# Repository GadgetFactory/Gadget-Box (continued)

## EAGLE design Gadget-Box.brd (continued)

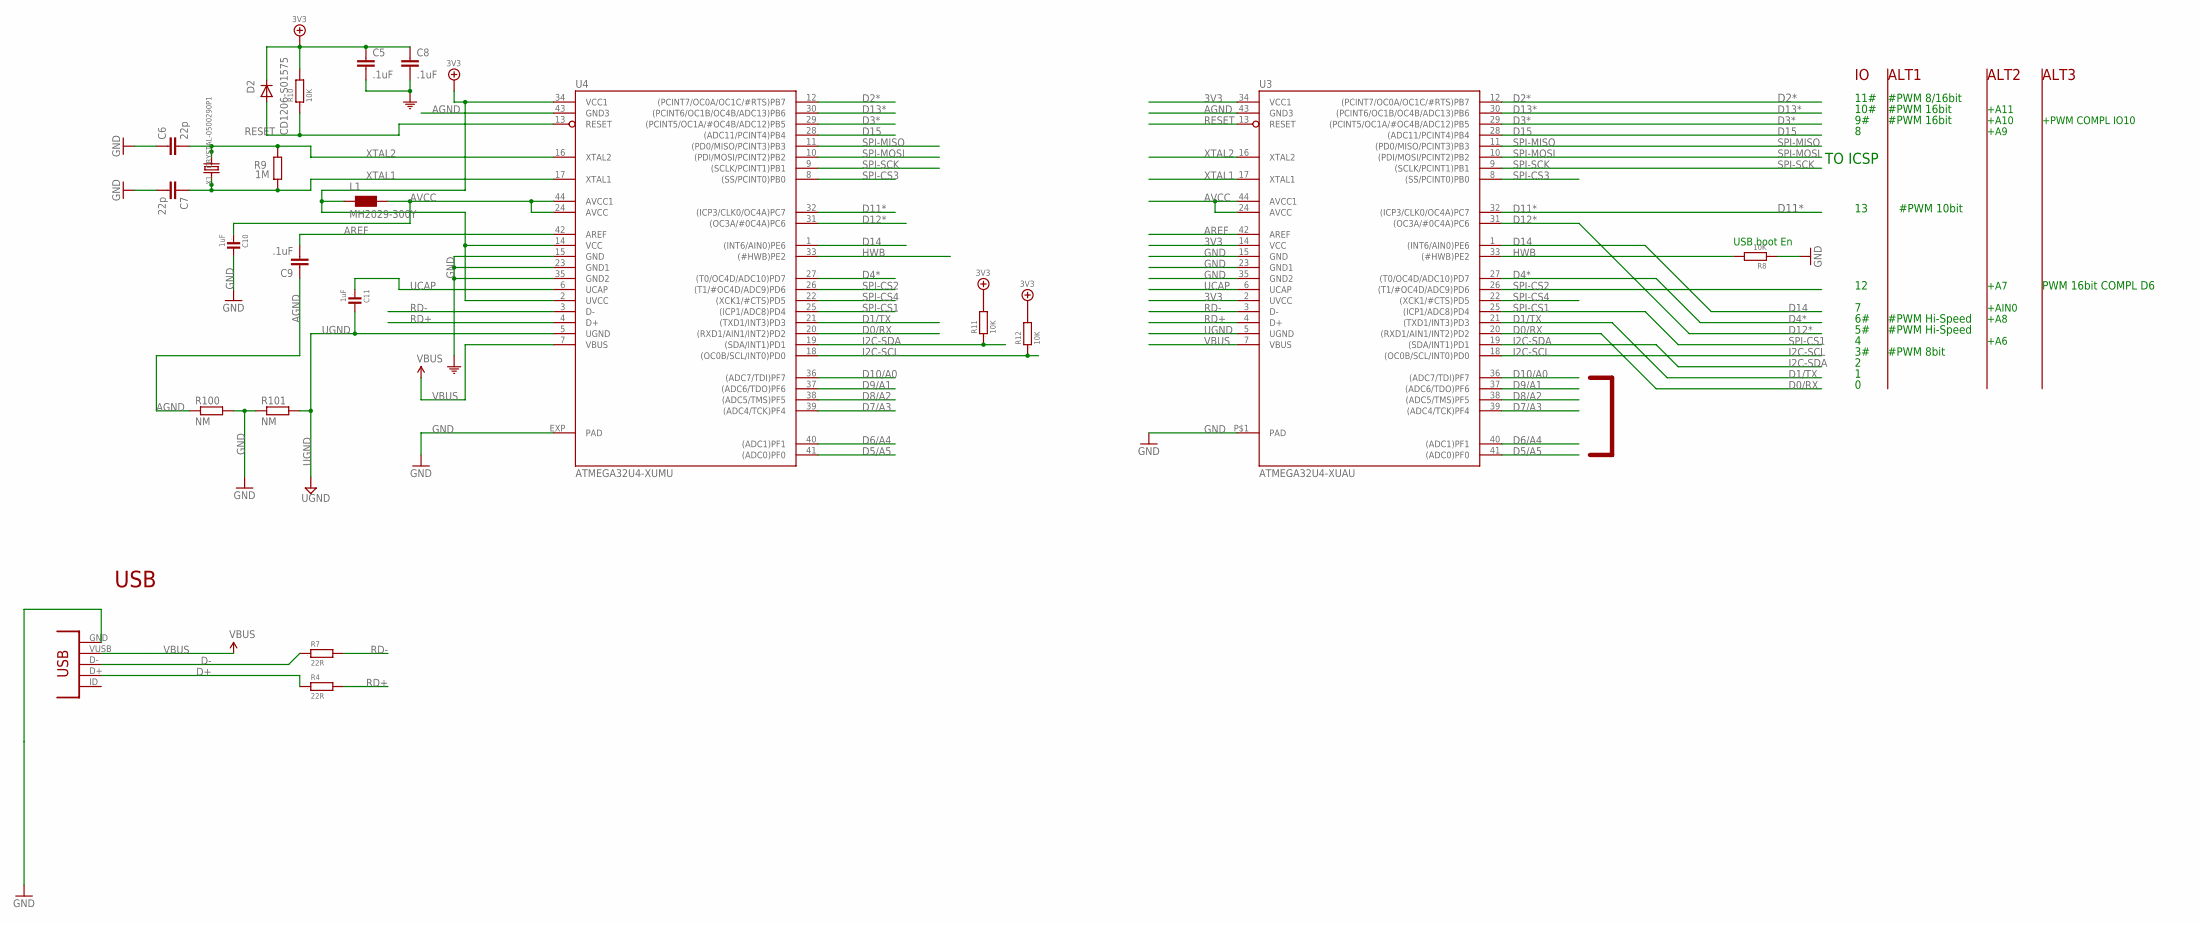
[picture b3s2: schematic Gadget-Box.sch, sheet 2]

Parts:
C5, C8, C9: .1uF; C0603-ROUND; PARTNO GRM188F51E104ZA01D,MURATA ELECTRONICS (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
C6, C7: 22p; C0603-ROUND; PARTNO C1608C0G1H220J080AA,TDK CORPORATION (VA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
C10, C11: 1uF; 0603; PARTNO C1608X5R1A105K080AC,TDK CORPORATION (VA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
D2: CD1206-S01575; MINIMELF; PARTNO CD1206-S01575,BOURNS INC (VA),dk,CD1206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
L1: MH2029-300Y; 0805; PARTNO MH2029-300Y,BOURNS INC (VA),dk,MH2029-3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
R4, R7: 22R; 0805; PARTNO RMCF0805JT22R0,STACKPOLE ELECTRONICS IN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
R8, R10, R11, R12: 10K; 0603; PARTNO RC0603JR-0710KL,YAGEO (VA),dk,311-10KGR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
R9: 1M; R0603-ROUND; PARTNO RMCF0603JT1M00,STACKPOLE ELECTRONICS IN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
R100, R101: NM; R0402
U3: ATMEGA32U4-XUAU; TQFP44-PAD; PARTNO ATMEGA32U4-AUR,ATMEL (VA),dk,ATMEGA32U4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
U4: ATMEGA32U4-XUMU; QFN44ML7X7
USB: CONN_USB; CONN_USB_MINI-B; PARTNO USB-M26FTR,ON SHORE TECHNOLOGY INC (VA)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
X1: CRYSTAL-0500290P1; 2P-SMD-5.0X3.2; PARTNO ABM3-8.000MHZ-D2Y-T,Abracon Corporation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

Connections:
3V3: C5.1, C8.1, D2.C, L1.1, R10.2, R11.2, R12.2, U3.2 (UVCC), U3.14 (VCC), U3.34 (VCC1), U4.2 (UVCC), U4.14 (VCC), U4.34 (VCC1); also elsewhere on the board
AGND: C9.1, R100.1, U3.43 (GND3), U4.43 (GND3)
AREF: C9.2, U3.42 (AREF), U4.42 (AREF)
AVCC: C10.1, L1.2, U3.24 (AVCC), U3.44 (AVCC1), U4.24 (AVCC), U4.44 (AVCC1)
D0/RX: U3.20 ((RXD1/AIN1/INT2)PD2), U4.20 ((RXD1/AIN1/INT2)PD2); also elsewhere on the board
D1/TX: U3.21 ((TXD1/INT3)PD3), U4.21 ((TXD1/INT3)PD3); also elsewhere on the board
D2*: U3.12 ((PCINT7/OC0A/OC1C/#RTS)PB7), U4.12 ((PCINT7/OC0A/OC1C/#RTS)PB7); also elsewhere on the board
D3*: U3.29 ((PCINT5/OC1A/#OC4B/ADC12)PB5), U4.29 ((PCINT5/OC1A/#OC4B/ADC12)PB5); also elsewhere on the board
D4*: U3.27 ((T0/OC4D/ADC10)PD7), U4.27 ((T0/OC4D/ADC10)PD7); also elsewhere on the board
D5/A5: U3.41 ((ADC0)PF0), U4.41 ((ADC0)PF0); also elsewhere on the board
D6/A4: U3.40 ((ADC1)PF1), U4.40 ((ADC1)PF1); also elsewhere on the board
D7/A3: U3.39 ((ADC4/TCK)PF4), U4.39 ((ADC4/TCK)PF4); also elsewhere on the board
D8/A2: U3.38 ((ADC5/TMS)PF5), U4.38 ((ADC5/TMS)PF5); also elsewhere on the board
D9/A1: U3.37 ((ADC6/TDO)PF6), U4.37 ((ADC6/TDO)PF6); also elsewhere on the board
D10/A0: U3.36 ((ADC7/TDI)PF7), U4.36 ((ADC7/TDI)PF7); also elsewhere on the board
D11*: U3.32 ((ICP3/CLK0/OC4A)PC7), U4.32 ((ICP3/CLK0/OC4A)PC7); also elsewhere on the board
D12*: U3.31 ((OC3A/#0C4A)PC6), U4.31 ((OC3A/#0C4A)PC6); also elsewhere on the board
D13*: U3.30 ((PCINT6/OC1B/OC4B/ADC13)PB6), U4.30 ((PCINT6/OC1B/OC4B/ADC13)PB6); also elsewhere on the board
D14: U3.1 ((INT6/AIN0)PE6), U4.1 ((INT6/AIN0)PE6); also elsewhere on the board
D15: U3.28 ((ADC11/PCINT4)PB4), U4.28 ((ADC11/PCINT4)PB4); also elsewhere on the board
D+: R4.1, USB.D+
D-: R7.1, USB.D-
GND: C5.2, C6.1, C7.2, C8.2, C10.2, R8.1, R100.2, R101.1, U3.15 (GND), U3.23 (GND1), U3.35 (GND2), U3.P$1 (PAD), U4.15 (GND), U4.23 (GND1), U4.35 (GND2), U4.EXP (PAD), USB.GND; also elsewhere on the board
HWB: R8.2, U3.33 ((#HWB)PE2), U4.33 ((#HWB)PE2)
I2C-SCL: R12.1, U3.18 ((OC0B/SCL/INT0)PD0), U4.18 ((OC0B/SCL/INT0)PD0); also elsewhere on the board
I2C-SDA: R11.1, U3.19 ((SDA/INT1)PD1), U4.19 ((SDA/INT1)PD1); also elsewhere on the board
RD+: R4.2, U3.4 (D+), U4.4 (D+)
RD-: R7.2, U3.3 (D-), U4.3 (D-)
RESET: D2.A, R10.1, U3.13 (RESET), U4.13 (RESET); also elsewhere on the board
SPI-CS1: U3.25 ((ICP1/ADC8)PD4), U4.25 ((ICP1/ADC8)PD4); also elsewhere on the board
SPI-CS2: U3.26 ((T1/#OC4D/ADC9)PD6), U4.26 ((T1/#OC4D/ADC9)PD6); also elsewhere on the board
SPI-CS3: U3.8 ((SS/PCINT0)PB0), U4.8 ((SS/PCINT0)PB0); also elsewhere on the board
SPI-CS4: U3.22 ((XCK1/#CTS)PD5), U4.22 ((XCK1/#CTS)PD5); also elsewhere on the board
SPI-MISO: U3.11 ((PD0/MISO/PCINT3)PB3), U4.11 ((PD0/MISO/PCINT3)PB3); also elsewhere on the board
SPI-MOSI: U3.10 ((PDI/MOSI/PCINT2)PB2), U4.10 ((PDI/MOSI/PCINT2)PB2); also elsewhere on the board
SPI-SCK: U3.9 ((SCLK/PCINT1)PB1), U4.9 ((SCLK/PCINT1)PB1); also elsewhere on the board
UCAP: C11.1, U3.6 (UCAP), U4.6 (UCAP)
UGND: C11.2, R101.2, U3.5 (UGND), U4.5 (UGND)
VBUS: U3.7 (VBUS), U4.7 (VBUS), USB.VUSB; also elsewhere on the board
XTAL1: C7.1, R9.1, U3.17 (XTAL1), U4.17 (XTAL1), X1.1
XTAL2: C6.2, R9.2, U3.16 (XTAL2), U4.16 (XTAL2), X1.2

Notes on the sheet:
USB boot En
USB
TO ICSP
10#
11#
#PWM 8bit
#PWM Hi-Speed
#PWM 8/16bit
#PWM 16bit
PWM 16bit COMPL D6
#PWM 10bit
+A6
+A7
+A11
+A10
+A8
+A9
+PWM COMPL IO10
+AIN0
ALT1
ALT2
ALT3

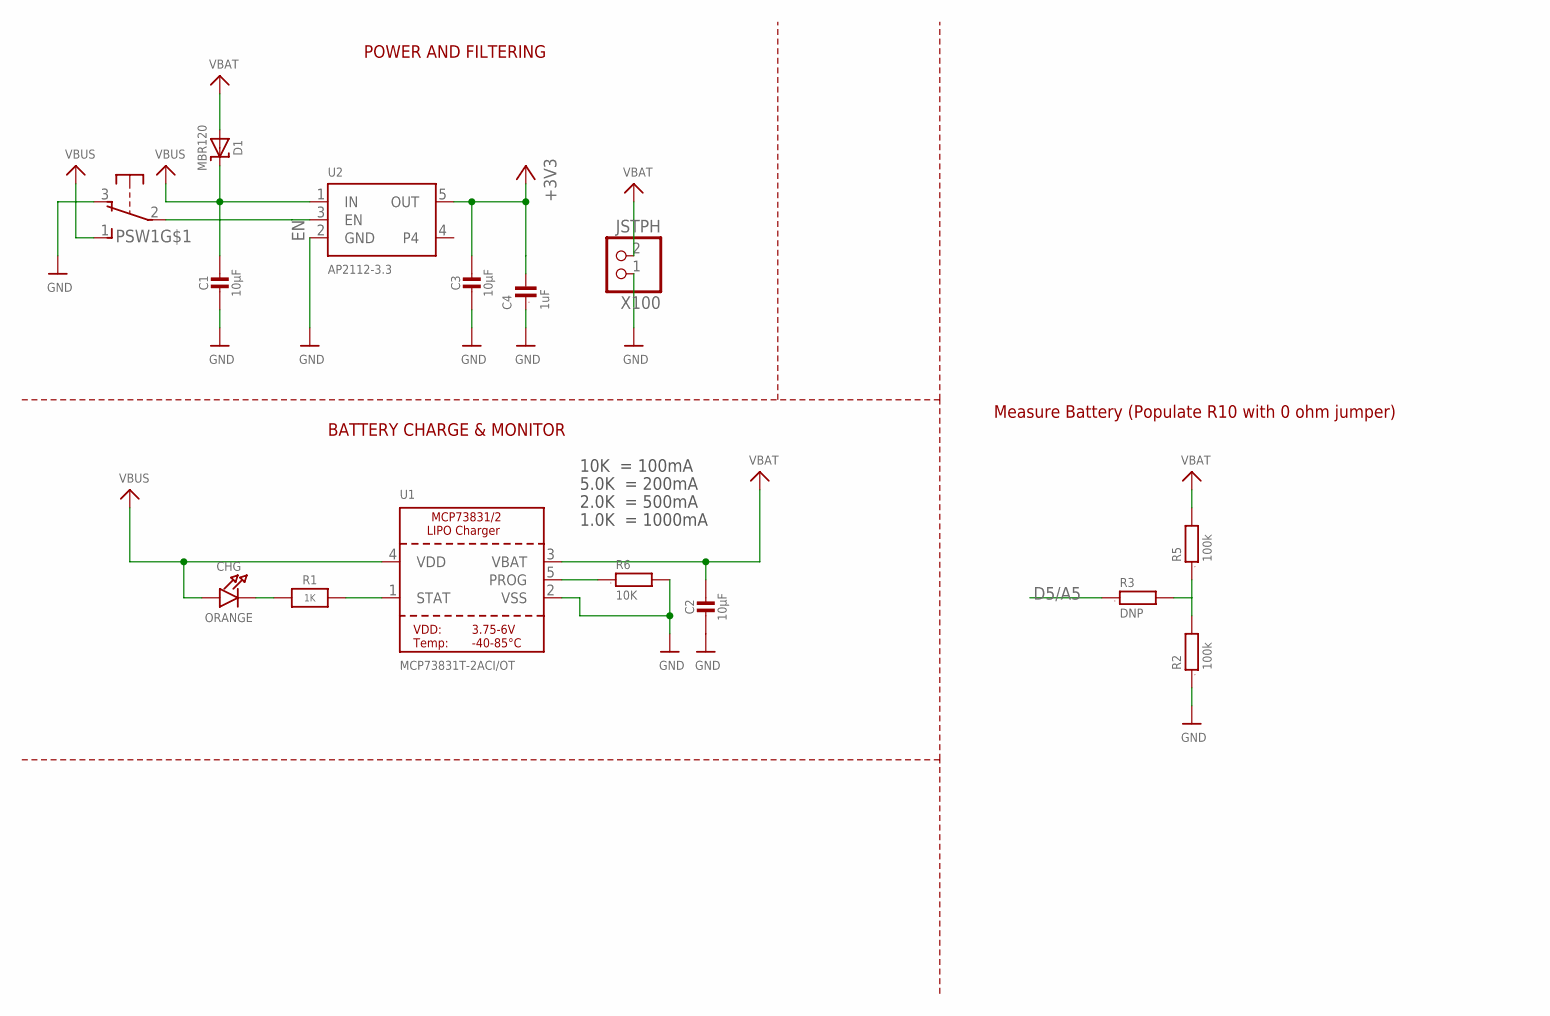
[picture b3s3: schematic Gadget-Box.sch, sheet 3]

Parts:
C1, C2, C3: 10µF; 0805-NO; PARTNO CL21F106ZPFNNNE,Samsung,DK,1276-3012-1-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
C4: 1uF; 0603; PARTNO C1608X5R1A105K080AC,TDK CORPORATION (VA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
CHG: ORANGE; CHIPLED_0805_NOOUTLINE; PARTNO LTST-C171EKT,LITE-ON INC (VA),DK,160-14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
D1: MBR120; SOD-123; PARTNO MBR120VLSFT3G,on semiconductor,dk,MBR12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
PSW1: OS102011MA1Q; PARTNO OS102011MA1QN1,C&K Components,dk,CKN955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
R1: 1K; 0603-NO; PARTNO RC0603JR-071KL,YAGEO (VA),dk,311-1.0KGR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
R2, R5: 100k; 0603; PARTNO RC0603JR-07100KL,YAGEO (VA),dk,311-100K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
R3: DNP; 0603
R6: 10K; 0603; PARTNO RC0603JR-0710KL,YAGEO (VA),dk,311-10KGR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
U1: MCP73831T-2ACI/OT; SOT23-5; PARTNO MCP73831T-2ACI/OT,MICROCHIP TECHNOLOGY 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
U2: AP2112-3.3; SOT23-5; PARTNO AP2112K-3.3TRG1,Diodes Incorporated,dk,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
X100: JSTPH; JSTPH2; PARTNO S2B-PH-SM4-TB(LF)(SN),JST SALES AMERICA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

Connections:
3V3: C3.1, C4.2, U2.5 (OUT); also elsewhere on the board
D5/A5: R3.1; also elsewhere on the board
EN: PSW1.2, U2.3 (EN)
GND: C1.2, C2.2, C3.2, C4.1, PSW1.3 (O), R2.1, R6.2, U1.2 (VSS), U2.2 (GND), X100.1; also elsewhere on the board
unnamed: CHG.C, R1.1
unnamed: R2.2, R3.2, R5.1
unnamed: R1.2, U1.1 (STAT)
unnamed: R6.1, U1.5 (PROG)
VBAT: C2.1, D1.A, R5.2, U1.3 (VBAT), X100.2
VBUS: C1.1, CHG.A, D1.C, PSW1.1 (S), U1.4 (VDD), U2.1 (IN); also elsewhere on the board

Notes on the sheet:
POWER AND FILTERING
10K = 100mA
5.0K = 200mA
2.0K = 500mA
1.0K = 1000mA
BATTERY CHARGE & MONITOR
Measure Battery (Populate R10 with 0 ohm jumper)

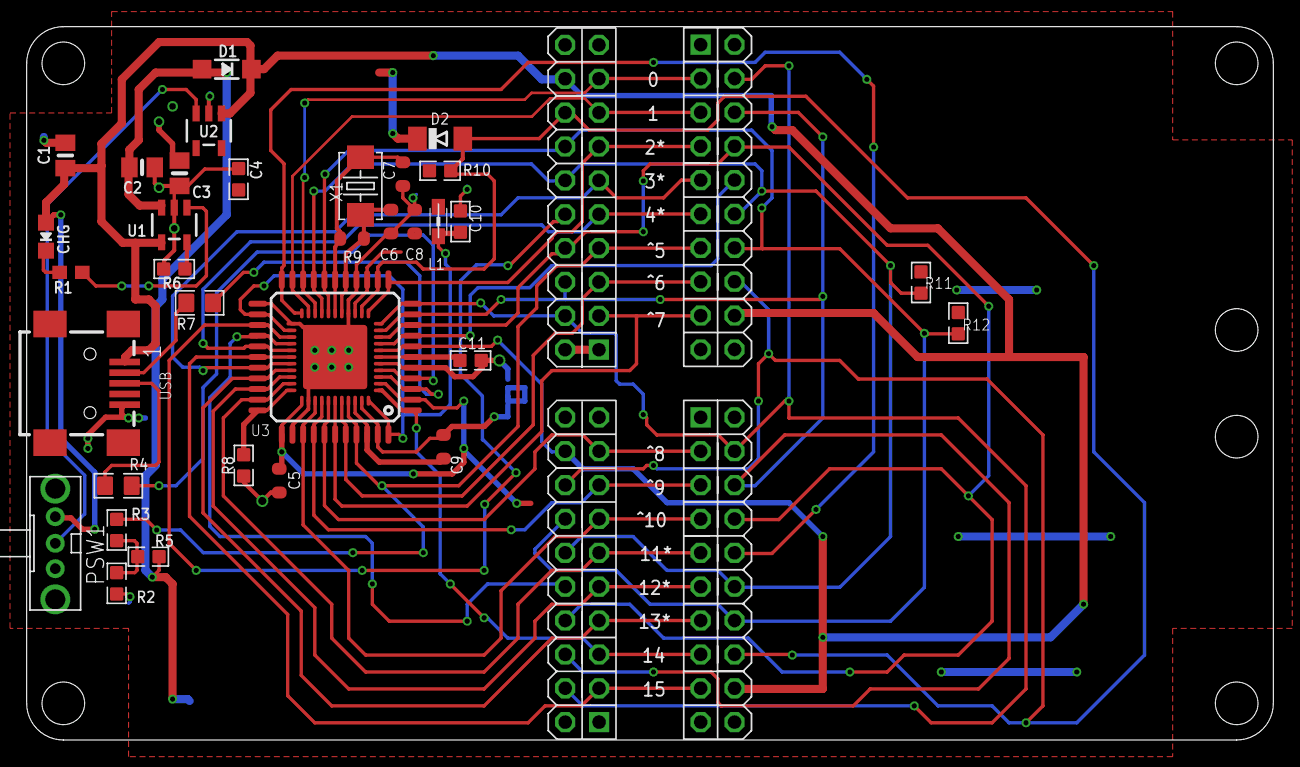
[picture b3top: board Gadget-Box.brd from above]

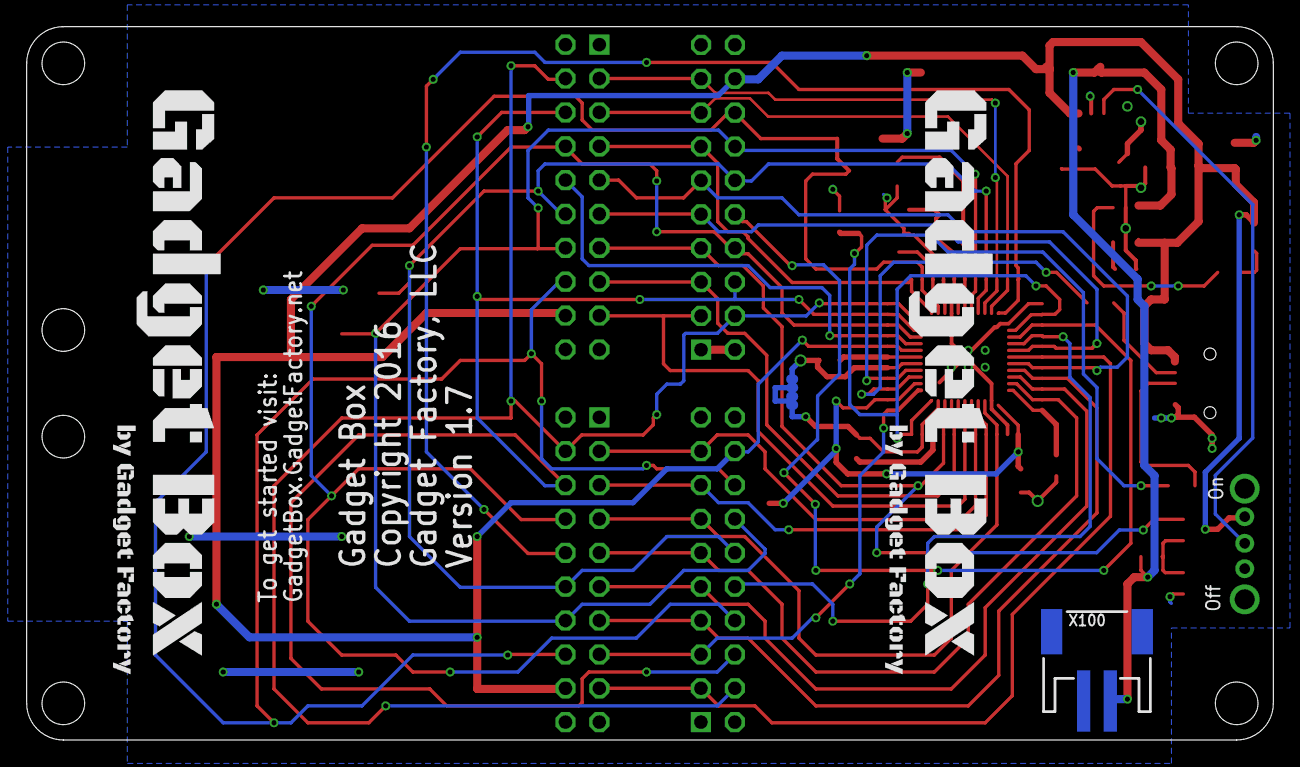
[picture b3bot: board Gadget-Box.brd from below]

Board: 2 copper layers, 93.5 x 53.5 mm, 44 parts (5 on the bottom side), 47 nets.

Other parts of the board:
$$U$1: ECOG93P53P5
U$100, U$101: GADGETBOX_TEXT

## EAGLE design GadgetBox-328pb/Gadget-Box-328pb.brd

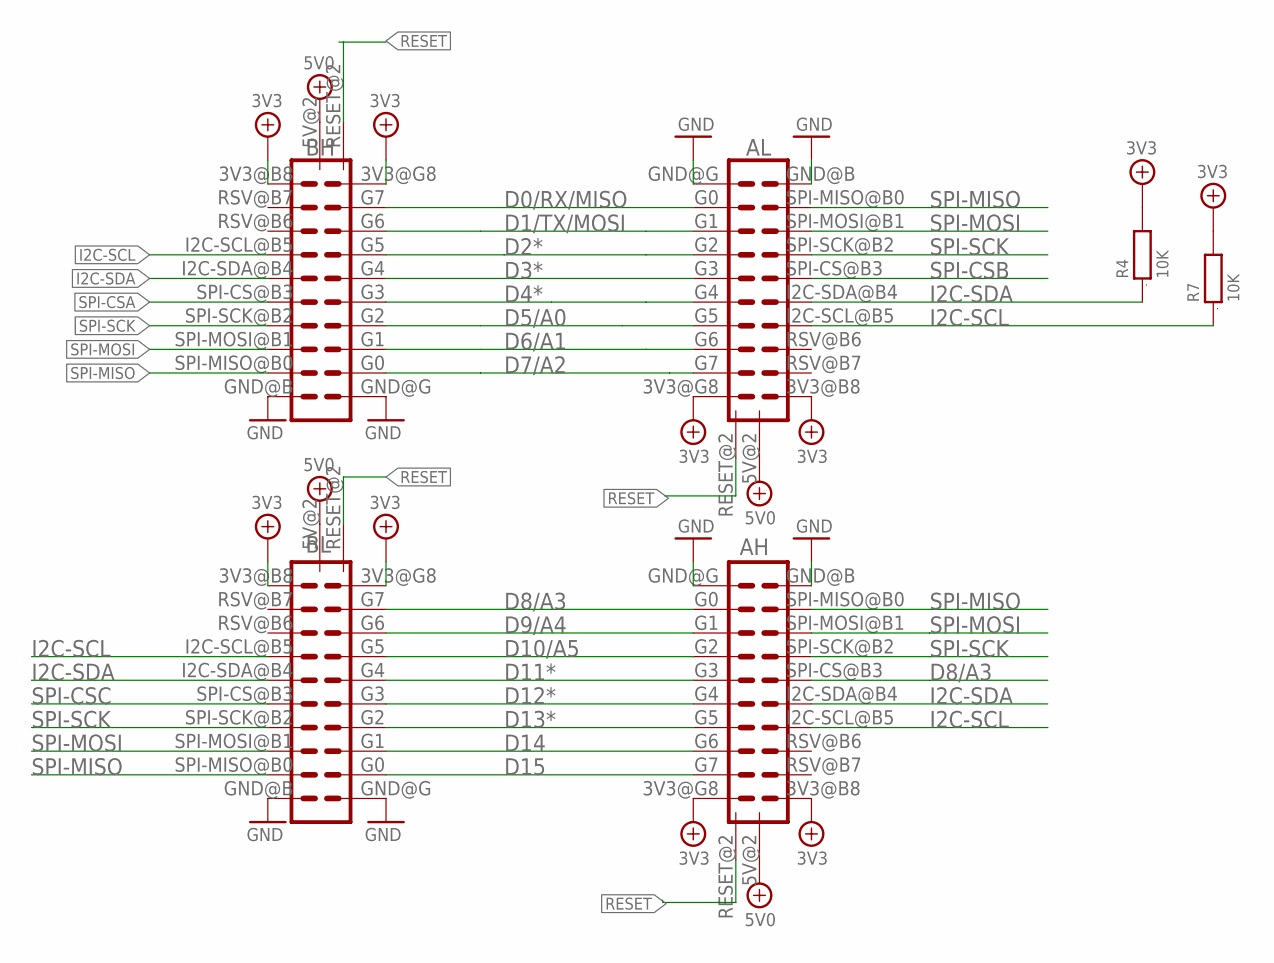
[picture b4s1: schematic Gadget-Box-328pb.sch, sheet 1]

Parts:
AH: ECOGECOG_SLOT_ALT1; ECOG_ALT1; PARTNO PPPC102LFBN-RC,SULLINS CONNECTOR SOLUTI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
AL: ECOGECOG_SLOT_ALT1; ECOG_ALT1; PARTNO PPPC102LFBN-RC,SULLINS CONNECTOR SOLUTI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
BH: ECOGECOG_SLOT_ALT1; ECOG_ALT1; PARTNO PPPC102LFBN-RC,SULLINS CONNECTOR SOLUTI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
BL: ECOGECOG_SLOT_ALT1; ECOG_ALT1; PARTNO PPPC102LFBN-RC,SULLINS CONNECTOR SOLUTI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
R4, R7: 10K; 0603; PARTNO RC0603JR-0710KL,YAGEO (VA),dk,311-10KGR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

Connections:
3V3: AH.3V3@B8 (3V3), AH.3V3@G8 (3V3), AL.3V3@B8 (3V3), AL.3V3@G8 (3V3), BH.3V3@B8 (3V3), BH.3V3@G8 (3V3), BL.3V3@B8 (3V3), BL.3V3@G8 (3V3), R4.2, R7.2; also elsewhere on the board
5V0: AH.5V@2 (5V), AL.5V@2 (5V), BH.5V@2 (5V), BL.5V@2 (5V); also elsewhere on the board
D0/RX/MISO: AL.G0, BH.G7; also elsewhere on the board
D1/TX/MOSI: AL.G1, BH.G6; also elsewhere on the board
D2*: AL.G2, BH.G5; also elsewhere on the board
D3*: AL.G3, BH.G4; also elsewhere on the board
D4*: AL.G4, BH.G3; also elsewhere on the board
D5/A0: AL.G5, BH.G2; also elsewhere on the board
D6/A1: AL.G6, BH.G1; also elsewhere on the board
D7/A2: AL.G7, BH.G0; also elsewhere on the board
D8/A3: AH.G0, AH.SPI-CS@B3 (SPI-CS), BL.G7; also elsewhere on the board
D9/A4: AH.G1, BL.G6; also elsewhere on the board
D10/A5: AH.G2, BL.G5; also elsewhere on the board
D11*: AH.G3, BL.G4; also elsewhere on the board
D12*: AH.G4, BL.G3; also elsewhere on the board
D13*: AH.G5, BL.G2; also elsewhere on the board
D14: AH.G6, BL.G1; also elsewhere on the board
D15: AH.G7, BL.G0; also elsewhere on the board
GND: AH.GND@B (GND), AH.GND@G (GND), AL.GND@B (GND), AL.GND@G (GND), BH.GND@B (GND), BH.GND@G (GND), BL.GND@B (GND), BL.GND@G (GND); also elsewhere on the board
I2C-SCL: AH.I2C-SCL@B5 (I2C-SCL), AL.I2C-SCL@B5 (I2C-SCL), BH.I2C-SCL@B5 (I2C-SCL), BL.I2C-SCL@B5 (I2C-SCL), R7.1; also elsewhere on the board
I2C-SDA: AH.I2C-SDA@B4 (I2C-SDA), AL.I2C-SDA@B4 (I2C-SDA), BH.I2C-SDA@B4 (I2C-SDA), BL.I2C-SDA@B4 (I2C-SDA), R4.1; also elsewhere on the board
RESET: AH.RESET@2 (RESET), AL.RESET@2 (RESET), BH.RESET@2 (RESET), BL.RESET@2 (RESET); also elsewhere on the board
SPI-CSA: BH.SPI-CS@B3 (SPI-CS); also elsewhere on the board
SPI-CSB: AL.SPI-CS@B3 (SPI-CS); also elsewhere on the board
SPI-CSC: BL.SPI-CS@B3 (SPI-CS); also elsewhere on the board
SPI-MISO: AH.SPI-MISO@B0 (SPI-MISO), AL.SPI-MISO@B0 (SPI-MISO), BH.SPI-MISO@B0 (SPI-MISO), BL.SPI-MISO@B0 (SPI-MISO); also elsewhere on the board
SPI-MOSI: AH.SPI-MOSI@B1 (SPI-MOSI), AL.SPI-MOSI@B1 (SPI-MOSI), BH.SPI-MOSI@B1 (SPI-MOSI), BL.SPI-MOSI@B1 (SPI-MOSI); also elsewhere on the board
SPI-SCK: AH.SPI-SCK@B2 (SPI-SCK), AL.SPI-SCK@B2 (SPI-SCK), BH.SPI-SCK@B2 (SPI-SCK), BL.SPI-SCK@B2 (SPI-SCK); also elsewhere on the board

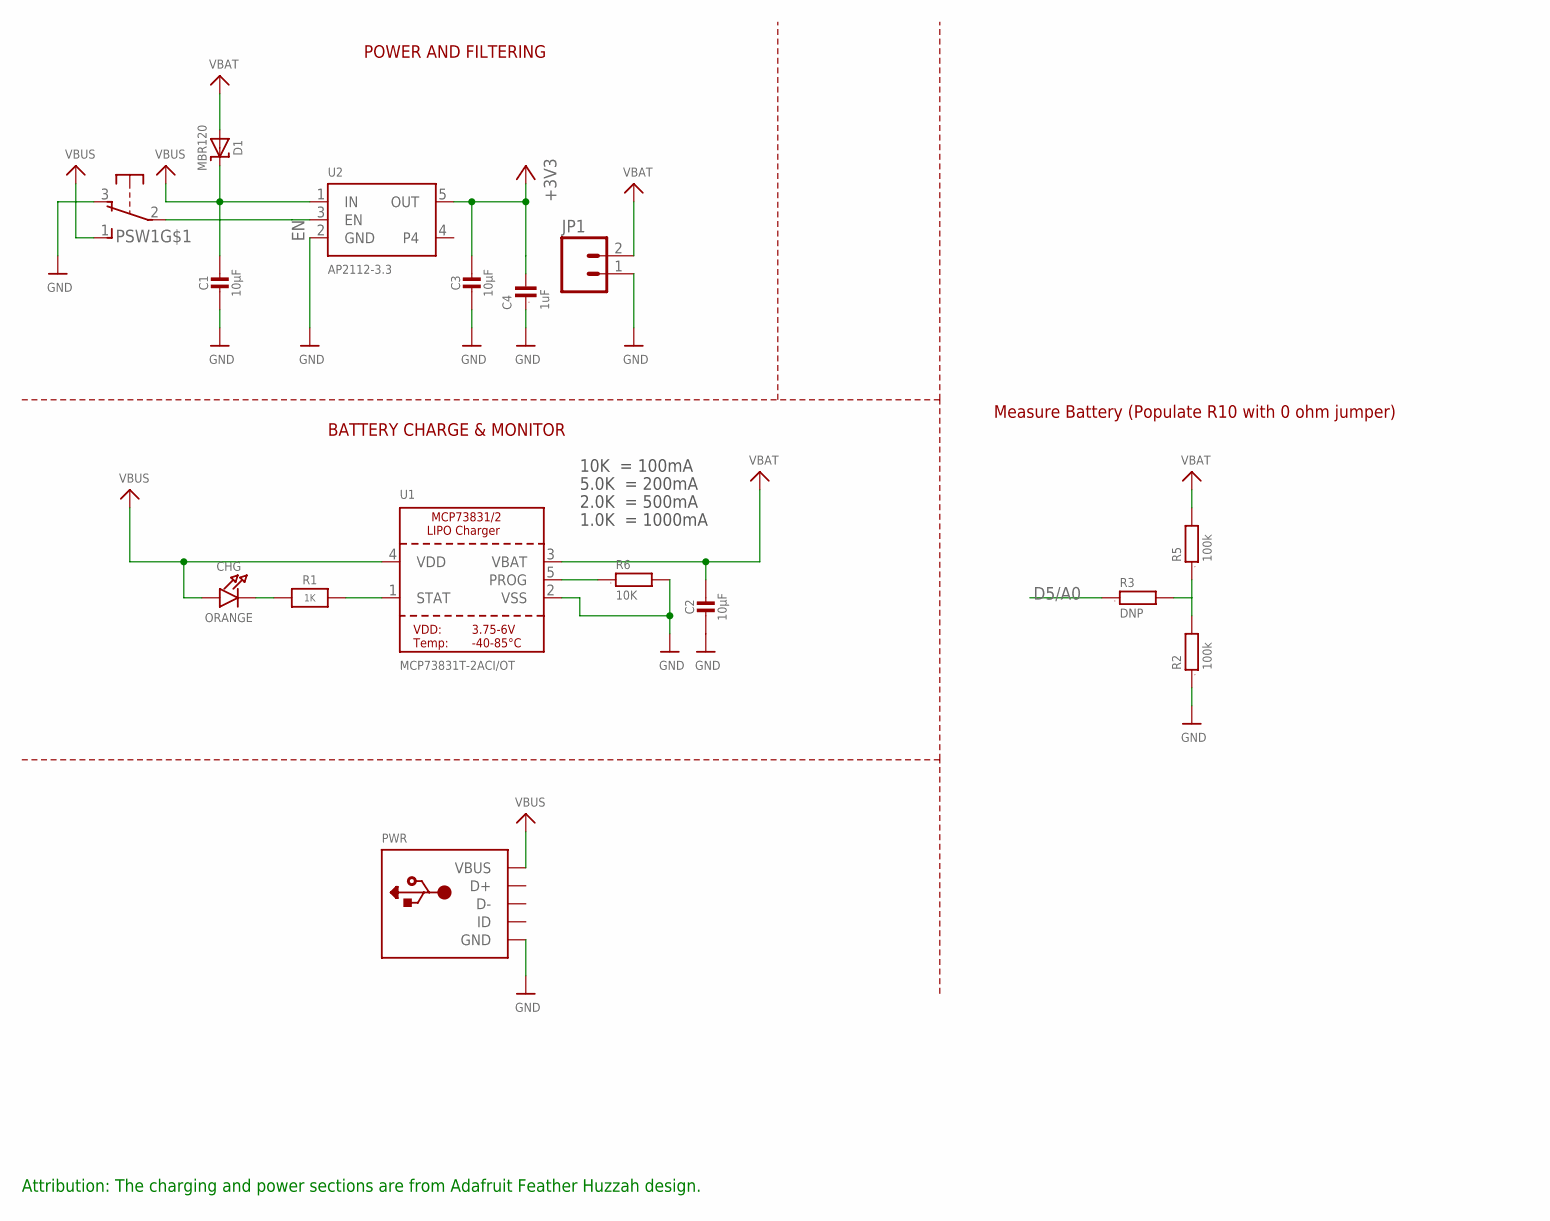
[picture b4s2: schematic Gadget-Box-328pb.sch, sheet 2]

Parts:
C1, C2, C3: 10µF; 0805-NO; PARTNO CL21F106ZPFNNNE,Samsung,DK,1276-3012-1-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
C4: 1uF; 0603; PARTNO C1608X5R1A105K080AC,TDK CORPORATION (VA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
CHG: ORANGE; CHIPLED_0805_NOOUTLINE; PARTNO LTST-C171EKT,LITE-ON INC (VA),DK,160-14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
D1: MBR120; SOD-123; PARTNO MBR120VLSFT3G,on semiconductor,dk,MBR12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
JP1: M02-JST-2-PTH-NO_SILK; JST-2-PTH-NS; PARTNO B2B-PH-SM4-TB(LF)(SN),JST SALES AMERICA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
PSW1: OS102011MA1Q; PARTNO OS102011MA1QN1,C&K Components,dk,CKN955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
PWR: USBMINIB; USB-MINIB; PARTNO USB-M26FTR,On Shore Technology Inc,DK,E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
R1: 1K; 0603-NO; PARTNO RC0603JR-071KL,YAGEO (VA),dk,311-1.0KGR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
R2, R5: 100k; 0603; PARTNO RC0603JR-07100KL,YAGEO (VA),dk,311-100K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
R3: DNP; 0603
R6: 10K; 0603; PARTNO RC0603JR-0710KL,YAGEO (VA),dk,311-10KGR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
U1: MCP73831T-2ACI/OT; SOT23-5; PARTNO MCP73831T-2ACI/OT,MICROCHIP TECHNOLOGY 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
U2: AP2112-3.3; SOT23-5; PARTNO AP2112K-3.3TRG1,Diodes Incorporated,dk,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

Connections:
3V3: C3.1, C4.2, U2.5 (OUT); also elsewhere on the board
5V0: C1.1, CHG.A, D1.C, PSW1.1 (S), PWR.VBUS, U1.4 (VDD), U2.1 (IN); also elsewhere on the board
D5/A0: R3.1; also elsewhere on the board
EN: PSW1.2, U2.3 (EN)
GND: C1.2, C2.2, C3.2, C4.1, JP1.1, PSW1.3 (O), PWR.GND, R2.1, R6.2, U1.2 (VSS), U2.2 (GND); also elsewhere on the board
unnamed: CHG.C, R1.1
unnamed: R2.2, R3.2, R5.1
unnamed: R1.2, U1.1 (STAT)
unnamed: R6.1, U1.5 (PROG)
VBAT: C2.1, D1.A, JP1.2, R5.2, U1.3 (VBAT)

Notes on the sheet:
POWER AND FILTERING
10K = 100mA
5.0K = 200mA
2.0K = 500mA
1.0K = 1000mA
BATTERY CHARGE & MONITOR
Measure Battery (Populate R10 with 0 ohm jumper)
Attribution: The charging and power sections are from Adafruit Feather Huzzah design.

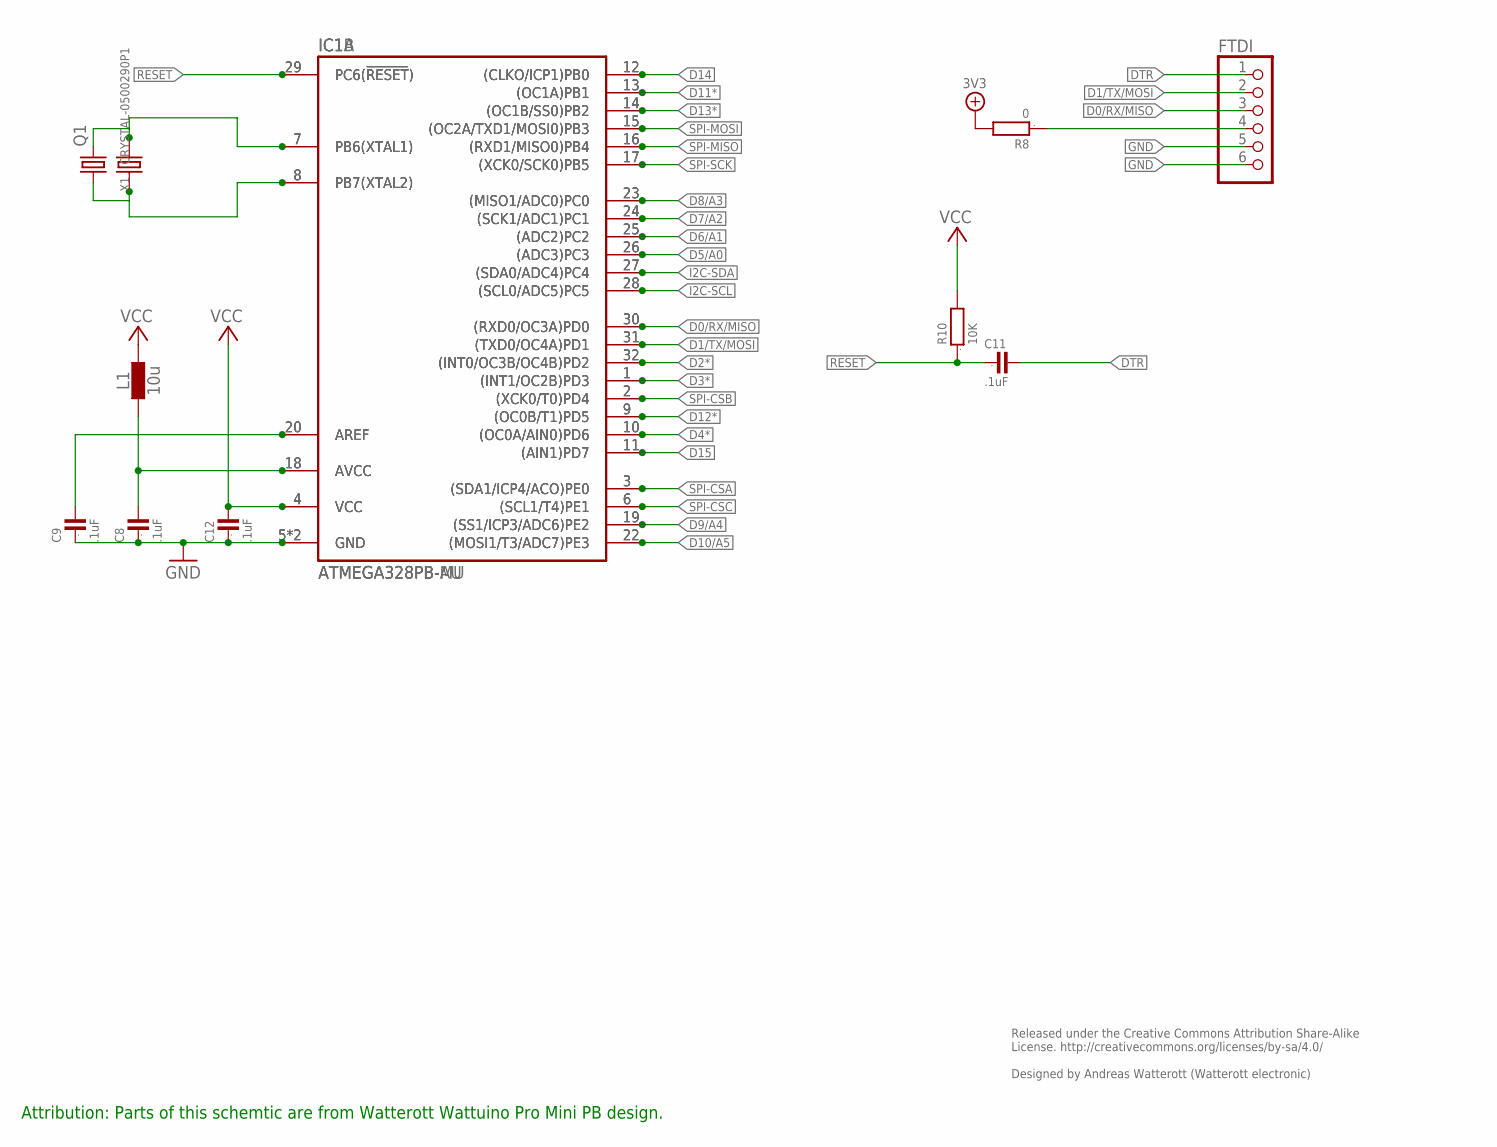
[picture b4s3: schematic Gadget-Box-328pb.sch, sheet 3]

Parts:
C8, C9, C11, C12: .1uF; 0805; PARTNO GRM21BR71E104KA01L,MURATA ELECTRONICS (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
FTDI: PINHD-1X6; 1X06; PARTNO PPPC061LGBN-RC,SULLINS CONNECTOR SOLUTI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
IC1A: ATMEGA328PB-AU; TQFP32; PARTNO ATMEGA328PB-AUR,ATMEL (VA),dk,ATMEGA328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
IC1B: ATMEGA328PB-MU; QFN32-PAD
L1: 10u; C0603; PARTNO MLZ1608E100M,TDK CORPORATION (VA),dk,44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
Q1: CRYSTALSM49; SM49; PARTNO ABLS-8.000MHZ-B4-T,Abracon Corporation,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
R8: 0; 0603
R10: 10K; 0603; PARTNO RC0603JR-0710KL,YAGEO (VA),dk,311-10KGR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
X1: CRYSTAL-0500290P1; 2P-SMD-5.0X3.2; PARTNO ABM3-8.000MHZ-D2Y-T,Abracon Corporation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

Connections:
3V3: C12.2, IC1A.4 (VCC), IC1B.4 (VCC), L1.2, R8.2, R10.2; also elsewhere on the board
AREF: C9.2, IC1A.20 (AREF), IC1B.20 (AREF)
AVCC: C8.2, IC1A.18 (AVCC), IC1B.18 (AVCC), L1.1
D0/RX/MISO: FTDI.3, IC1A.30 ((RXD0/OC3A)PD0), IC1B.30 ((RXD0/OC3A)PD0); also elsewhere on the board
D1/TX/MOSI: FTDI.2, IC1A.31 ((TXD0/OC4A)PD1), IC1B.31 ((TXD0/OC4A)PD1); also elsewhere on the board
D2*: IC1A.32 ((INT0/OC3B/OC4B)PD2), IC1B.32 ((INT0/OC3B/OC4B)PD2); also elsewhere on the board
D3*: IC1A.1 ((INT1/OC2B)PD3), IC1B.1 ((INT1/OC2B)PD3); also elsewhere on the board
D4*: IC1A.10 ((OC0A/AIN0)PD6), IC1B.10 ((OC0A/AIN0)PD6); also elsewhere on the board
D5/A0: IC1A.26 ((ADC3)PC3), IC1B.26 ((ADC3)PC3); also elsewhere on the board
D6/A1: IC1A.25 ((ADC2)PC2), IC1B.25 ((ADC2)PC2); also elsewhere on the board
D7/A2: IC1A.24 ((SCK1/ADC1)PC1), IC1B.24 ((SCK1/ADC1)PC1); also elsewhere on the board
D8/A3: IC1A.23 ((MISO1/ADC0)PC0), IC1B.23 ((MISO1/ADC0)PC0); also elsewhere on the board
D9/A4: IC1A.19 ((SS1/ICP3/ADC6)PE2), IC1B.19 ((SS1/ICP3/ADC6)PE2); also elsewhere on the board
D10/A5: IC1A.22 ((MOSI1/T3/ADC7)PE3), IC1B.22 ((MOSI1/T3/ADC7)PE3); also elsewhere on the board
D11*: IC1A.13 ((OC1A)PB1), IC1B.13 ((OC1A)PB1); also elsewhere on the board
D12*: IC1A.9 ((OC0B/T1)PD5), IC1B.9 ((OC0B/T1)PD5); also elsewhere on the board
D13*: IC1A.14 ((OC1B/SS0)PB2), IC1B.14 ((OC1B/SS0)PB2); also elsewhere on the board
D14: IC1A.12 ((CLKO/ICP1)PB0), IC1B.12 ((CLKO/ICP1)PB0); also elsewhere on the board
D15: IC1A.11 ((AIN1)PD7), IC1B.11 ((AIN1)PD7); also elsewhere on the board
DTR: C11.2, FTDI.1
GND: C8.1, C9.1, C12.1, FTDI.5, FTDI.6, IC1A.5 (GND), IC1A.21 (GND), IC1B.5 (GND), IC1B.21 (GND); also elsewhere on the board
I2C-SCL: IC1A.28 ((SCL0/ADC5)PC5), IC1B.28 ((SCL0/ADC5)PC5); also elsewhere on the board
I2C-SDA: IC1A.27 ((SDA0/ADC4)PC4), IC1B.27 ((SDA0/ADC4)PC4); also elsewhere on the board
unnamed: IC1A.8 (PB7(XTAL2)), IC1B.8 (PB7(XTAL2)), Q1.1, X1.1
unnamed: IC1A.7 (PB6(XTAL1)), IC1B.7 (PB6(XTAL1)), Q1.2, X1.2
unnamed: FTDI.4, R8.1
RESET: C11.1, IC1A.29 (PC6(!RESET!)), IC1B.29 (PC6(!RESET!)), R10.1; also elsewhere on the board
SPI-CSA: IC1A.3 ((SDA1/ICP4/ACO)PE0), IC1B.3 ((SDA1/ICP4/ACO)PE0); also elsewhere on the board
SPI-CSB: IC1A.2 ((XCK0/T0)PD4), IC1B.2 ((XCK0/T0)PD4); also elsewhere on the board
SPI-CSC: IC1A.6 ((SCL1/T4)PE1), IC1B.6 ((SCL1/T4)PE1); also elsewhere on the board
SPI-MISO: IC1A.16 ((RXD1/MISO0)PB4), IC1B.16 ((RXD1/MISO0)PB4); also elsewhere on the board
SPI-MOSI: IC1A.15 ((OC2A/TXD1/MOSI0)PB3), IC1B.15 ((OC2A/TXD1/MOSI0)PB3); also elsewhere on the board
SPI-SCK: IC1A.17 ((XCK0/SCK0)PB5), IC1B.17 ((XCK0/SCK0)PB5); also elsewhere on the board

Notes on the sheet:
Released under the Creative Commons Attribution Share-Alike License. http://creativecommons.org/licenses/by-sa/4.0/ Designed by Andreas Watterott (Watterott electronic)
Attribution: Parts of this schemtic are from Watterott Wattuino Pro Mini PB design.

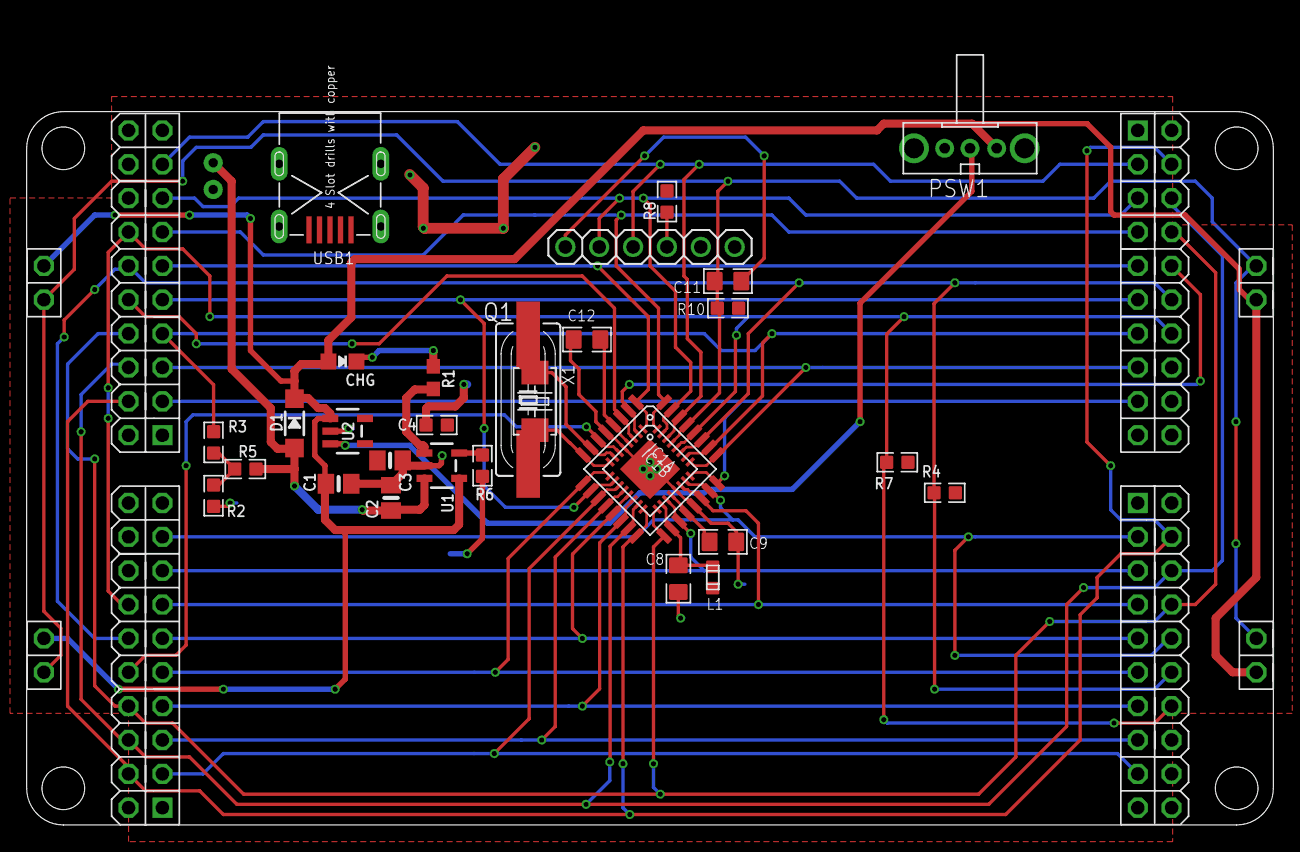
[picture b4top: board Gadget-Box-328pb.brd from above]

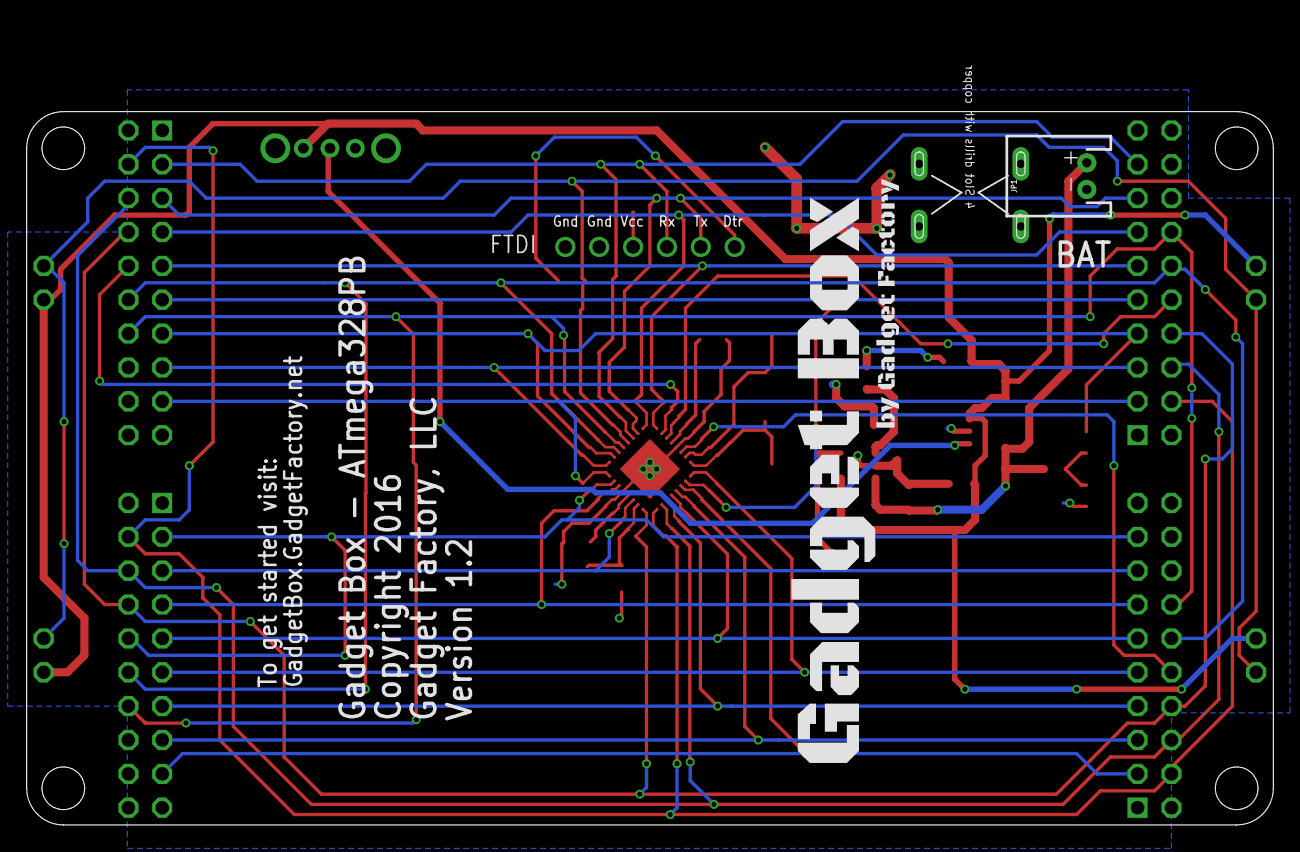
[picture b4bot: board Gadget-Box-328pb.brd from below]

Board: 2 copper layers, 93.5 x 53.5 mm, 36 parts (2 on the bottom side), 40 nets.

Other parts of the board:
$$U$1: ECOG93P53P5
U$100: GADGETBOX_TEXT
USB1: ST-USB-013A; MINIUSB5+4P-0.8-90D

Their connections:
GND: USB1.GND@1, USB1.GND@2, USB1.GND@3, USB1.GND@4; also elsewhere on the board
